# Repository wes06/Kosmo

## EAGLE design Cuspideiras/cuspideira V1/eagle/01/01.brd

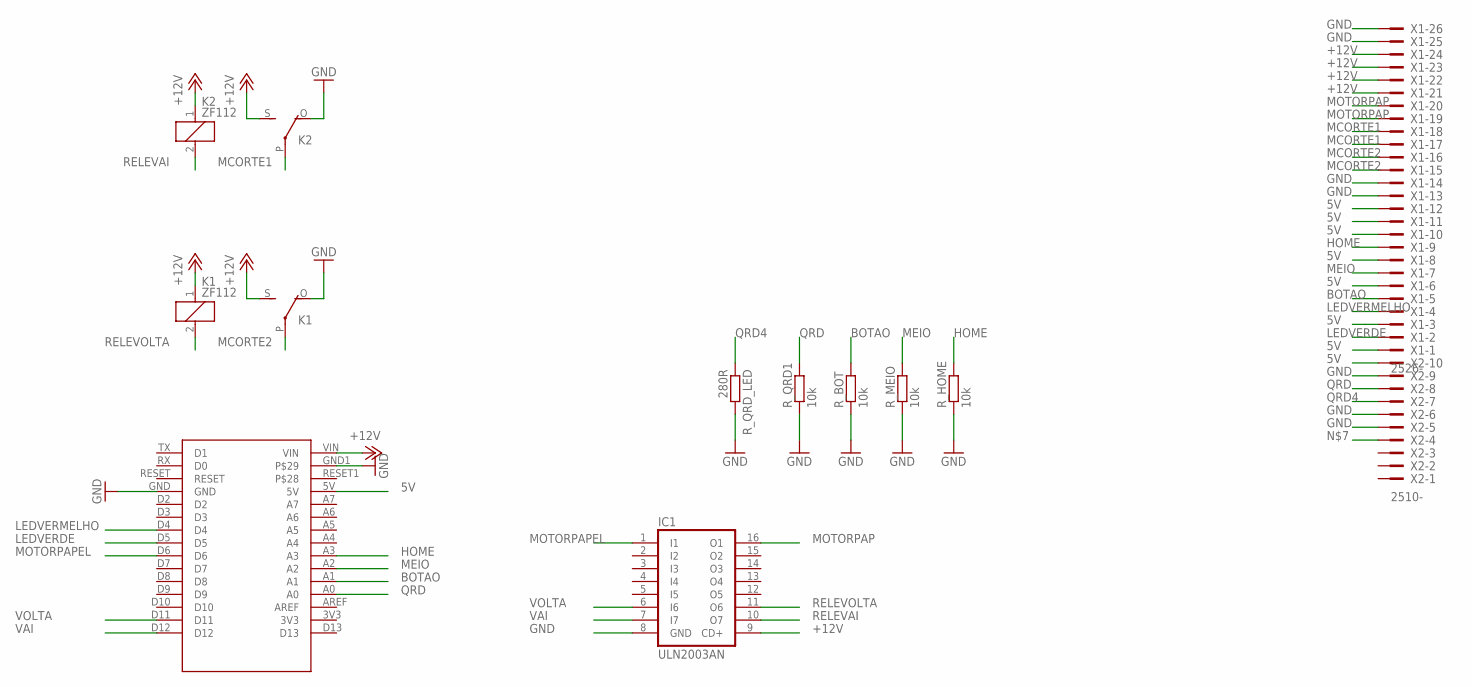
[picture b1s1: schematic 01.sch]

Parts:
IC1: ULN2003AN; DIL16
K1, K2: ZF112
R_BOT: 10k; 0207/15
R_HOME: 10k; 0207/15
R_MEIO: 10k; 0207/15
R_QRD1: 10k; 0207/15
R_QRD_LED: 280R; 0204/7
U$1: ARDUINONANO; NANO
X1: 2526-; PAK100/2500-26
X2: 2510-; PAK100/2500-10

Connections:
5V: U$1.5V, X1.1, X1.3, X1.6, X1.8, X1.10, X1.11, X1.12, X2.10
+12V: IC1.9 (CD+), K1.1, K1.S, K2.1, K2.S, U$1.VIN, X1.21, X1.22, X1.23, X1.24
BOTAO: R_BOT.2, U$1.A1, X1.5
GND: IC1.8 (GND), K1.O, K2.O, R_BOT.1, R_HOME.1, R_MEIO.1, R_QRD1.1, R_QRD_LED.2, U$1.GND, U$1.GND1, X1.13, X1.14, X1.25, X1.26, X2.5, X2.6, X2.9
HOME: R_HOME.2, U$1.A3, X1.9
LEDVERDE: U$1.D5, X1.2
LEDVERMELHO: U$1.D4, X1.4
MCORTE1: K2.P, X1.17, X1.18
MCORTE2: K1.P, X1.15, X1.16
MEIO: R_MEIO.2, U$1.A2, X1.7
MOTORPAP: IC1.16 (O1), X1.19, X1.20
MOTORPAPEL: IC1.1 (I1), U$1.D6
QRD: R_QRD1.2, U$1.A0, X2.8
QRD4: R_QRD_LED.1, X2.7
RELEVAI: IC1.10 (O7), K2.2
RELEVOLTA: IC1.11 (O6), K1.2
VAI: IC1.7 (I7), U$1.D12
VOLTA: IC1.6 (I6), U$1.D11

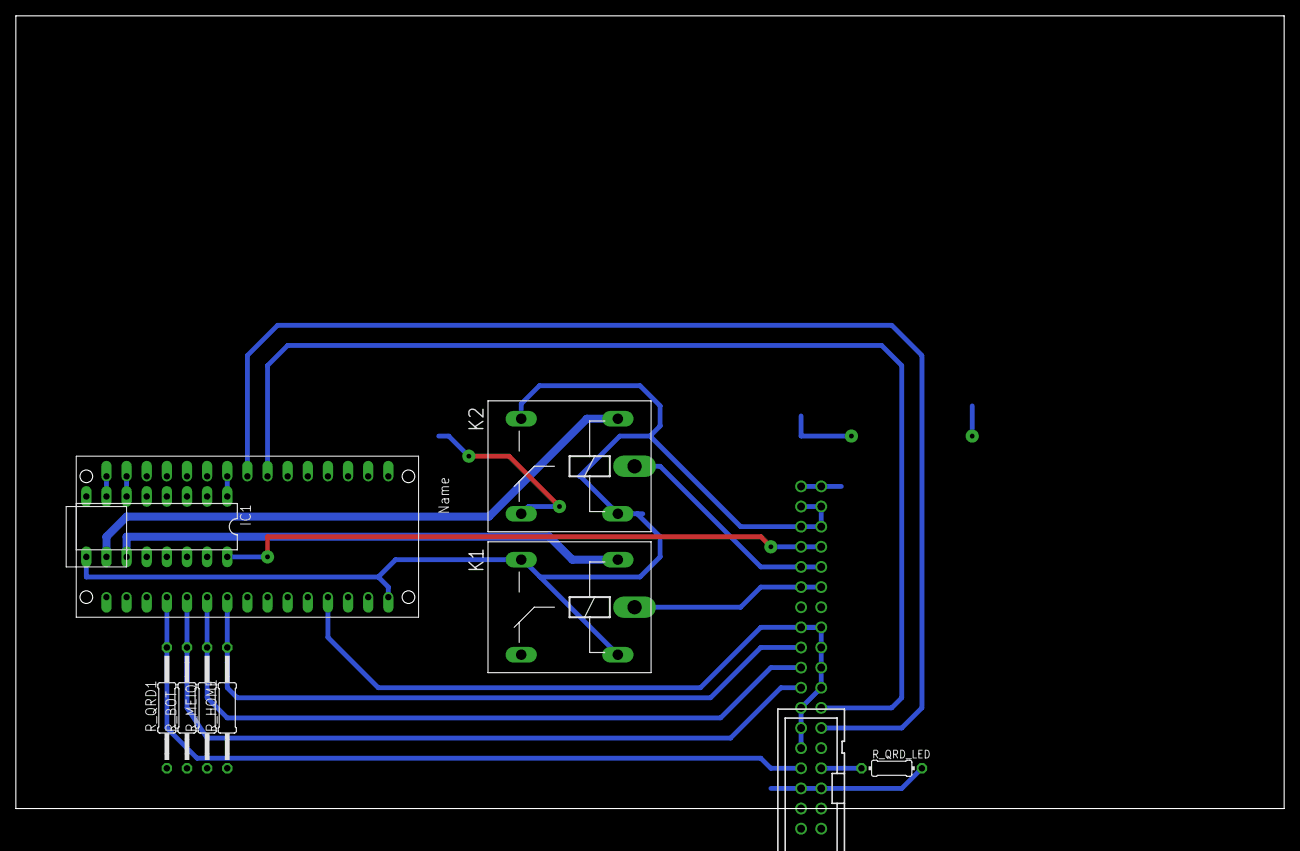
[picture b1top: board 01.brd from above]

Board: 2 copper layers, 160.0 x 100.0 mm, 11 parts (1 on the bottom side), 18 nets.

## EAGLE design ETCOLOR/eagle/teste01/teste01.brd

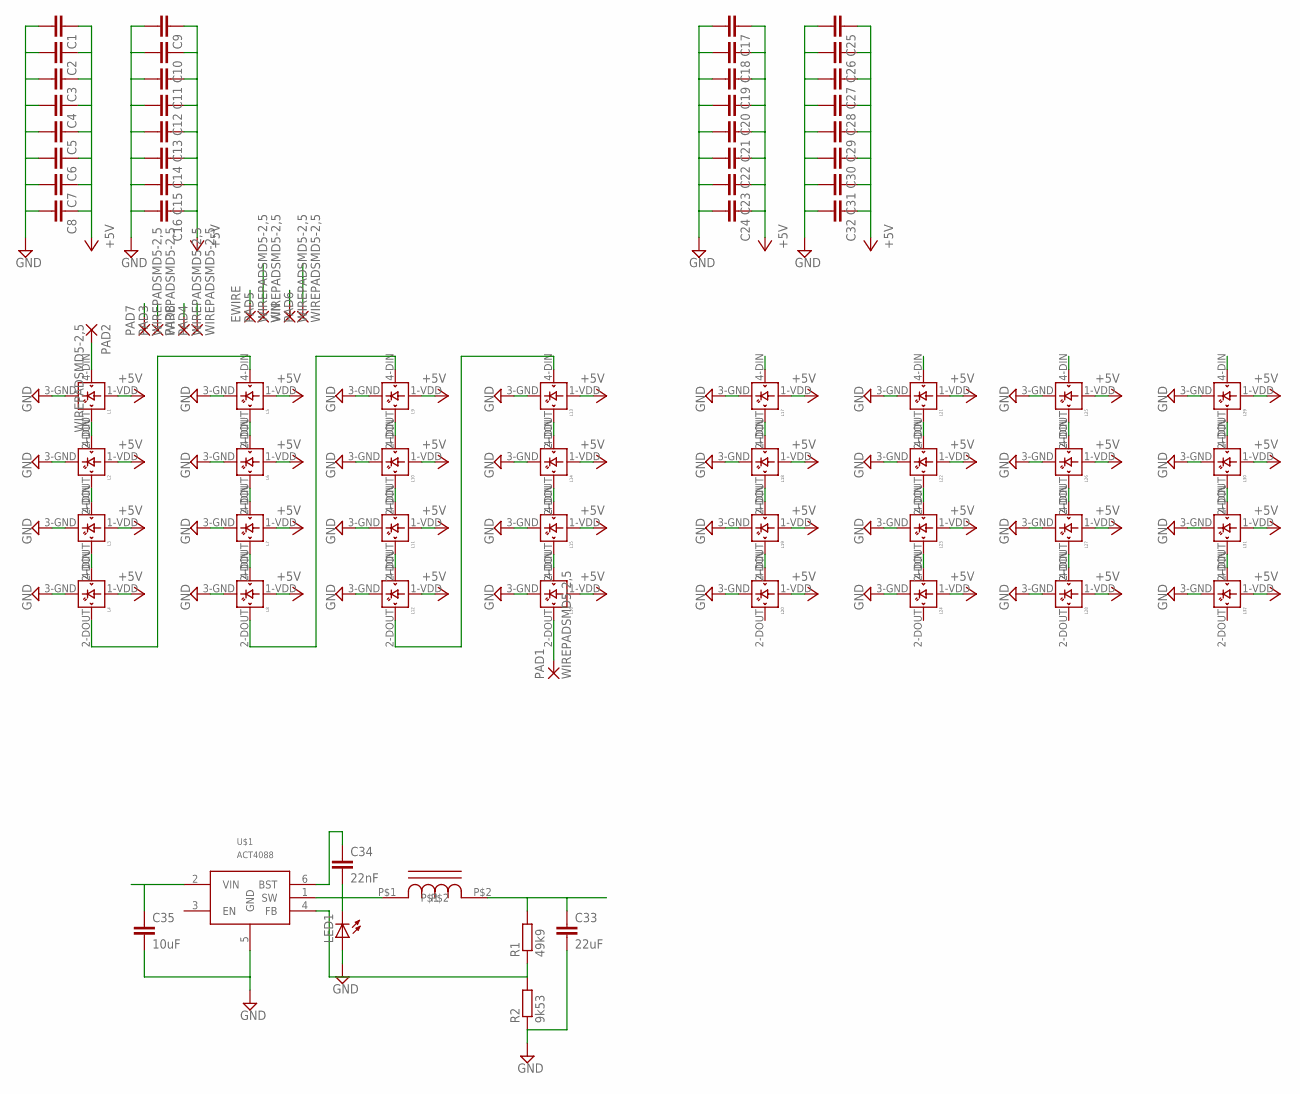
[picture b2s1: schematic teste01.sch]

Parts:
C1, C2, C3, C4, C5, C6, C7, C8, C9, C10, C11, C12, C13, C14, C15, C16, C17, C18, C19, C20, C21, C22, C23, C24, C25, C26, C27, C28, C29, C30, C31, C32: C-EUC0805K; C0805K
C33: 22uF; C1210
C34: 22nF; C0805
C35: 10uF; C1210
EWIRE: WIREPADSMD5-2,5; 5-2,5
L1, L2, L3, L4, L5, L6, L7, L8, L9, L10, L11, L12, L13, L14, L15, L16, L17, L18, L19, L20, L21, L22, L23, L24, L25, L26, L27, L28, L29, L30, L31, L32: WS2812B
LED1: LED1206; LED-1206
PAD1, PAD2, PAD3, PAD4, PAD5, PAD6, PAD7, PAD8: WIREPADSMD5-2,5; 5-2,5
R1: 49k9; M0805
R2: 9k53; M0805
U$1: ACT4088; SOT23-6
U$2: INDUCTOR; 6060
VIN: WIREPADSMD5-2,5; 5-2,5

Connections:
+5V: C1.1, C2.1, C3.1, C4.1, C5.1, C6.1, C7.1, C8.1, C9.1, C10.1, C11.1, C12.1, C13.1, C14.1, C15.1, C16.1, C17.1, C18.1, C19.1, C20.1, C21.1, C22.1, C23.1, C24.1, C25.1, C26.1, C27.1, C28.1, C29.1, C30.1, C31.1, C32.1, L1.1-VDD (VDD), L2.1-VDD (VDD), L3.1-VDD (VDD), L4.1-VDD (VDD), L5.1-VDD (VDD), L6.1-VDD (VDD), L7.1-VDD (VDD), L8.1-VDD (VDD), L9.1-VDD (VDD), L10.1-VDD (VDD), L11.1-VDD (VDD), L12.1-VDD (VDD), L13.1-VDD (VDD), L14.1-VDD (VDD), L15.1-VDD (VDD), L16.1-VDD (VDD), L17.1-VDD (VDD), L18.1-VDD (VDD), L19.1-VDD (VDD), L20.1-VDD (VDD), L21.1-VDD (VDD), L22.1-VDD (VDD), L23.1-VDD (VDD), L24.1-VDD (VDD), L25.1-VDD (VDD), L26.1-VDD (VDD), L27.1-VDD (VDD), L28.1-VDD (VDD), L29.1-VDD (VDD), L30.1-VDD (VDD), L31.1-VDD (VDD), L32.1-VDD (VDD)
GND: C1.2, C2.2, C3.2, C4.2, C5.2, C6.2, C7.2, C8.2, C9.2, C10.2, C11.2, C12.2, C13.2, C14.2, C15.2, C16.2, C17.2, C18.2, C19.2, C20.2, C21.2, C22.2, C23.2, C24.2, C25.2, C26.2, C27.2, C28.2, C29.2, C30.2, C31.2, C32.2, C33.2, C35.2, L1.3-GND (GND), L2.3-GND (GND), L3.3-GND (GND), L4.3-GND (GND), L5.3-GND (GND), L6.3-GND (GND), L7.3-GND (GND), L8.3-GND (GND), L9.3-GND (GND), L10.3-GND (GND), L11.3-GND (GND), L12.3-GND (GND), L13.3-GND (GND), L14.3-GND (GND), L15.3-GND (GND), L16.3-GND (GND), L17.3-GND (GND), L18.3-GND (GND), L19.3-GND (GND), L20.3-GND (GND), L21.3-GND (GND), L22.3-GND (GND), L23.3-GND (GND), L24.3-GND (GND), L25.3-GND (GND), L26.3-GND (GND), L27.3-GND (GND), L28.3-GND (GND), L29.3-GND (GND), L30.3-GND (GND), L31.3-GND (GND), L32.3-GND (GND), LED1.A, PAD3.1, PAD4.1, PAD7.1, PAD8.1, R2.1, U$1.5 (GND)
unnamed: L1.2-DOUT (DOUT), L2.4-DIN (DIN)
unnamed: L2.2-DOUT (DOUT), L3.4-DIN (DIN)
unnamed: L1.4-DIN (DIN), PAD2.1
unnamed: L3.2-DOUT (DOUT), L4.4-DIN (DIN)
unnamed: L4.2-DOUT (DOUT), L5.4-DIN (DIN)
unnamed: L5.2-DOUT (DOUT), L6.4-DIN (DIN)
unnamed: L6.2-DOUT (DOUT), L7.4-DIN (DIN)
unnamed: L7.2-DOUT (DOUT), L8.4-DIN (DIN)
unnamed: L8.2-DOUT (DOUT), L9.4-DIN (DIN)
unnamed: L9.2-DOUT (DOUT), L10.4-DIN (DIN)
unnamed: L10.2-DOUT (DOUT), L11.4-DIN (DIN)
unnamed: L11.2-DOUT (DOUT), L12.4-DIN (DIN)
unnamed: L12.2-DOUT (DOUT), L13.4-DIN (DIN)
unnamed: L13.2-DOUT (DOUT), L14.4-DIN (DIN)
unnamed: L14.2-DOUT (DOUT), L15.4-DIN (DIN)
unnamed: L15.2-DOUT (DOUT), L16.4-DIN (DIN)
unnamed: L17.2-DOUT (DOUT), L18.4-DIN (DIN)
unnamed: L18.2-DOUT (DOUT), L19.4-DIN (DIN)
unnamed: L19.2-DOUT (DOUT), L20.4-DIN (DIN)
unnamed: L21.2-DOUT (DOUT), L22.4-DIN (DIN)
unnamed: L22.2-DOUT (DOUT), L23.4-DIN (DIN)
unnamed: L23.2-DOUT (DOUT), L24.4-DIN (DIN)
unnamed: L25.2-DOUT (DOUT), L26.4-DIN (DIN)
unnamed: L26.2-DOUT (DOUT), L27.4-DIN (DIN)
unnamed: L27.2-DOUT (DOUT), L28.4-DIN (DIN)
unnamed: L29.2-DOUT (DOUT), L30.4-DIN (DIN)
unnamed: L30.2-DOUT (DOUT), L31.4-DIN (DIN)
unnamed: L31.2-DOUT (DOUT), L32.4-DIN (DIN)
unnamed: L16.2-DOUT (DOUT), PAD1.1
unnamed: C34.2, LED1.C, U$1.1 (SW), U$2.P$1
unnamed: C33.1, R1.2, U$2.P$2
unnamed: R1.1, R2.2, U$1.4 (FB)
unnamed: C34.1, U$1.6 (BST)
VIN: C35.1, EWIRE.1, PAD5.1, PAD6.1, U$1.2 (VIN), VIN.1

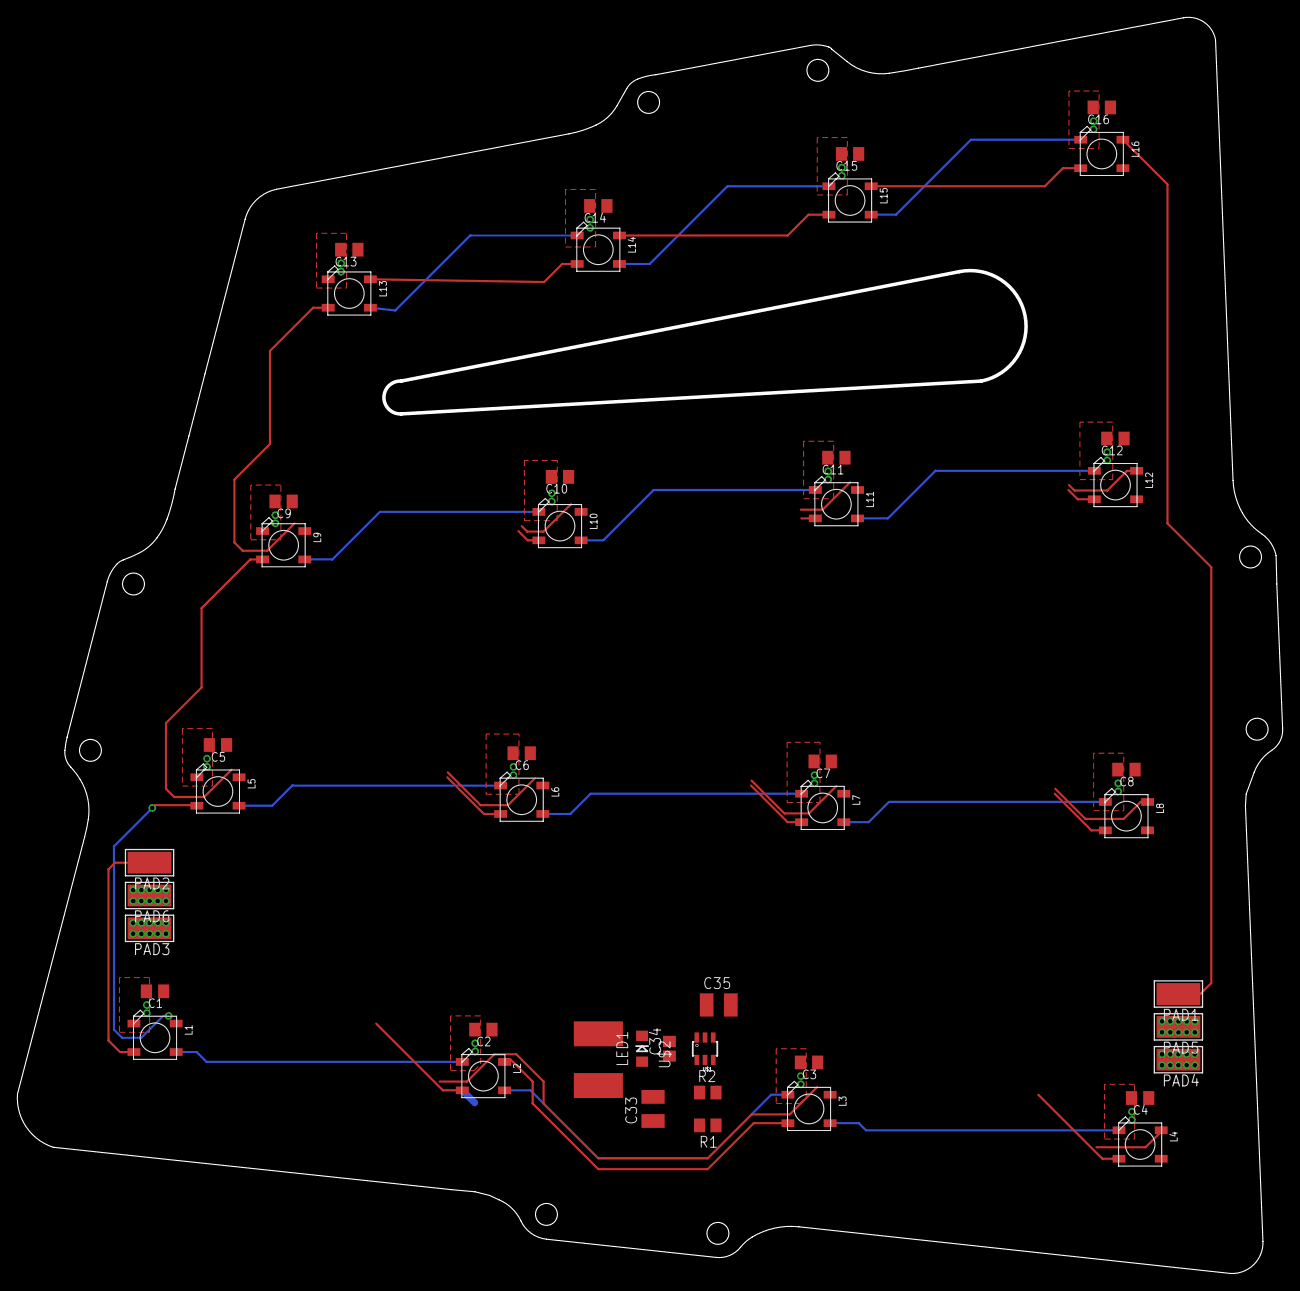
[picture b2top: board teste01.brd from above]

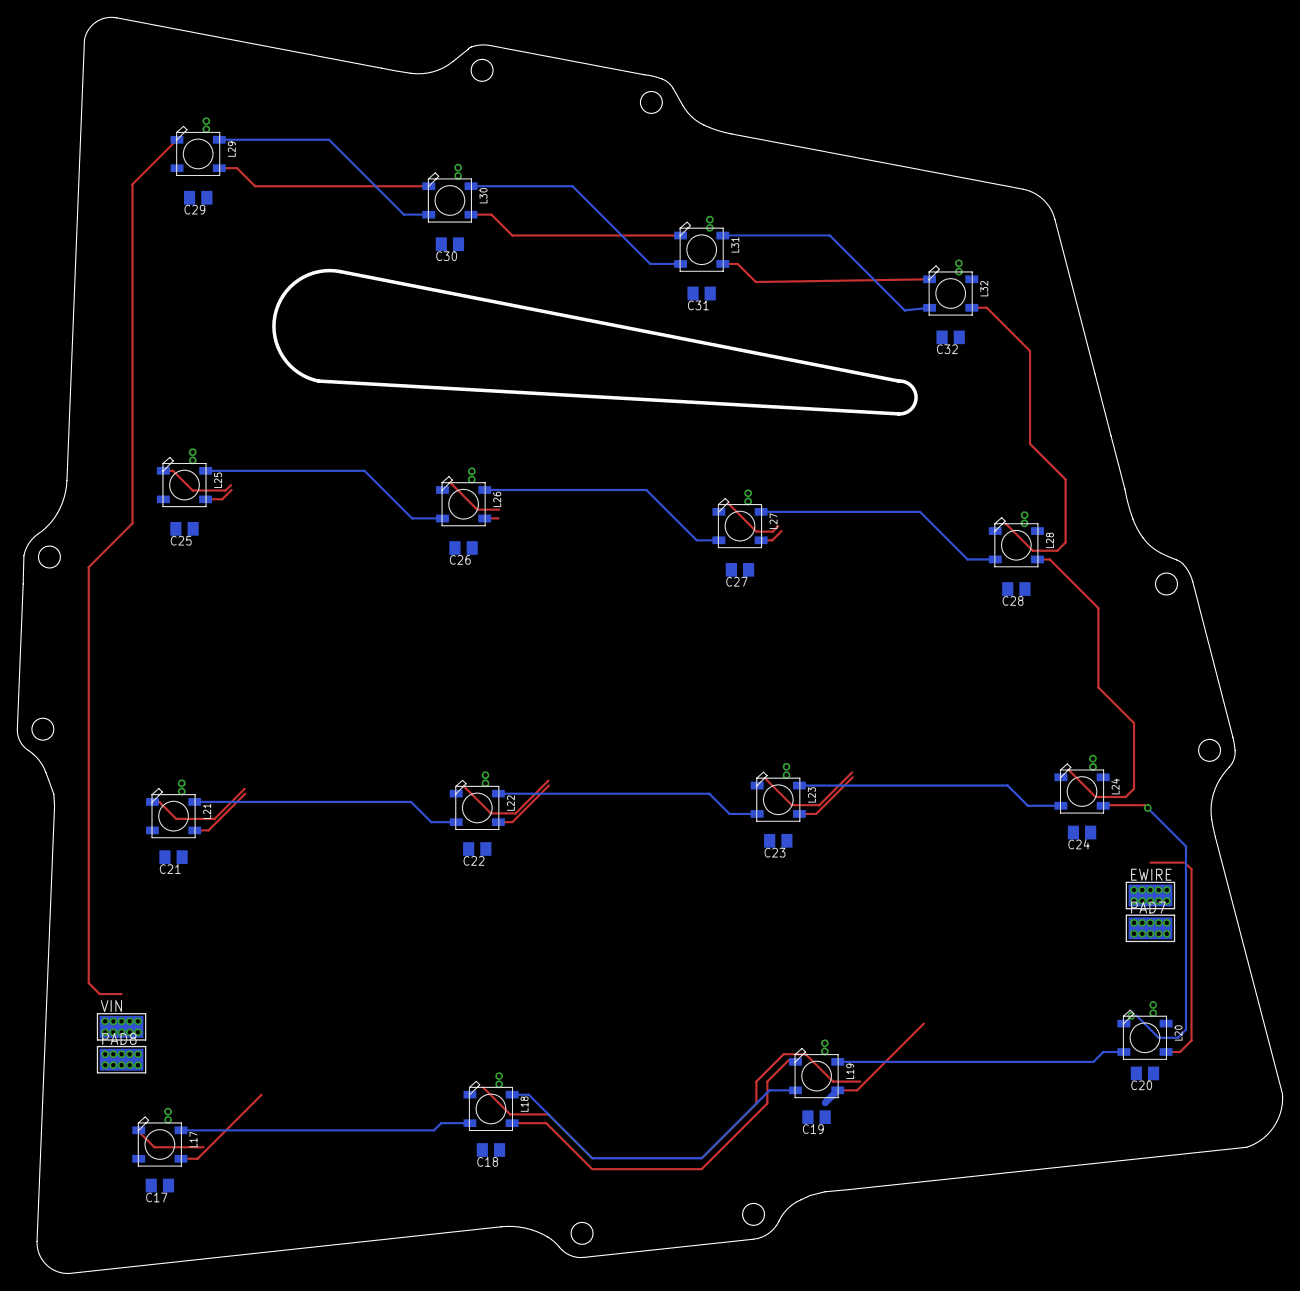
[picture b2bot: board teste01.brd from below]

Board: 2 copper layers, 146.8 x 145.8 mm, 82 parts (36 on the bottom side), 36 nets.

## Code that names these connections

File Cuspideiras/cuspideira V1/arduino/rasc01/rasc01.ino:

int stopHome = A3;//corrigidos
int stopMeio = A2;

int motPapel = 6;

int releVai = 12;
int releVolta = 11;


int ledVerd = 5;
int ledVerm = 4;

int botao = A1;

int qrd = A0;

int etapa = 99;

long debounceDelay = 50;

int buttonStateMeio = LOW;
int lastButtonStateMeio = LOW;

long lastDebounceTimeMeio = 0; 

int buttonStateHome = LOW;
int lastButtonStateHome = LOW;

long lastDebounceTimeHome = 0; 

int buttonStateBot = LOW;
int lastButtonStateBot = LOW;

long lastDebounceTimeBot = 0; 

boolean direcao =  HIGH;

void setup(){
  pinMode(stopHome, INPUT);
  pinMode(stopMeio, INPUT);
  pinMode(botao, INPUT);

  pinMode(motPapel, OUTPUT);
  pinMode(releVai, OUTPUT);
  pinMode(releVolta, OUTPUT);
  pinMode(ledVerd, OUTPUT);
  pinMode(ledVerm, OUTPUT);
}

void loopi(){

  motorVai();

  delay(1000);
  motorVolta();


  delay(1000);
  motorPara();
  delay(1000);
}

void loop(){
  //Serial.println("alouu");
  debounceHome();
  debounceMeio();
  debounceBot();

  if(etapa==99){
    corte();
  }

  if(etapa == 0 && buttonStateBot == LOW){
    etapa =1;
    direcao=HIGH;
    digitalWrite(ledVerm,HIGH);
    digitalWrite(ledVerd,LOW);
  }

  if(etapa==1){
    digitalWrite(motPapel, HIGH);
    delay(100);
    etapa=2;  
  }

  if(analogRead(qrd)<600 && etapa == 2){
    digitalWrite(motPapel, LOW);
    etapa=3;

  }
  
  if(etapa == 3){
    corte();
 }

  if(etapa ==4){

    digitalWrite(ledVerm,HIGH);
    digitalWrite(ledVerd,LOW);
    delay(10000);
    etapa = 0;  
    digitalWrite(ledVerm,LOW);
    digitalWrite(ledVerd,HIGH);
  }

}

void corte(){
if(direcao){
  motorVai();
}
  //Serial.println('4');

  //Serial.println(buttonStateMeio && direcao);
  //Serial.println(direcao);
  if(buttonStateMeio && direcao){
    motorVolta();
    direcao = LOW;
  }

  if(buttonStateHome && direcao ==LOW){
   // Serial.println('2');
    motorPara();
    direcao = HIGH;
    if(etapa==99){

      //Serial.println('1');
      digitalWrite(ledVerm,LOW);
      digitalWrite(ledVerd,HIGH);
      etapa = 0; 
    }
    if(etapa == 3){
      etapa =4;
    }
  }

}

void motorVai(){
  digitalWrite(motPapel, LOW);
  digitalWrite(releVai, LOW);
  digitalWrite(releVolta, HIGH);
}

void motorVolta(){
  digitalWrite(motPapel, LOW);
  digitalWrite(releVai, HIGH);
  digitalWrite(releVolta, LOW);
}

void motorPara(){
  digitalWrite(releVai, LOW);
  digitalWrite(releVolta, LOW);
}

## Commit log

2016-09-28 .gitignore added
2016-09-28 Eagle files cleanup
2016-09-28 Folder reorganizing
